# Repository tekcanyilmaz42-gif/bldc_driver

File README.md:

# BLDC / PMSM Motor Driver AI (KiCad 10 Project)

Bu depo, modüler BLDC / PMSM ve EESM motor sürücüsü donanım tasarımını (KiCad 10) içermektedir.

## 📁 Proje Yapısı

- `bldc_driver_ai.kicad_pro` / `.kicad_sch` / `.kicad_pcb`: Ana sistem projesi ve üst seviye bağlantılar
- `kontrol_karti.kicad_sch`: dsPIC tabanlı kontrol kartı şematiği
- `guc_karti.kicad_sch`: TO-220 MOSFET tabanlı yüksek akım güç katı ve 24× KOSHIN KLH (24 mF, 60 A rms) DC-link bara kondansatör grubu
- `gate_driver_u.kicad_sch`, `gate_driver_v.kicad_sch`, `gate_driver_w.kicad_sch`: Faz sürücü modülleri
- `eesm_modulu.kicad_sch`: EESM uyarma kontrol modülü
- `bldc_proje.pretty/` & `fp-lib-table`: Projeye özel footprint kütüphanesi (KOSHIN KLH radial elektrolitik, özel land pattern'ler)
- `montaj/`: 3D montaj modelleri (`.step`), mekanik yerleşim ve render görselleri
- `uretim/`: Modüllere ait üretim Gerber arşivleri (`.zip`), klasörleri ve SMD dizgi koordinat listeleri (`.csv`)
- `yardımcı_dokuman/`: Revizyon raporları, teknik analizler ve destekleyici dokümanlar
- `bldc_driver_ai_BOM.xlsx`: Güncel malzeme listesi (BOM)
- `SISTEM_REVIZYON_PLANI.md`: Kapsamlı sistem revizyon ve doğrulama planı

## 🛠️ Gereksinimler

- [KiCad 10.0+](https://www.kicad.org/) veya uyumlu sürüm

## 🔍 Tasarım İncelemesi 3: Bulgular ve Yapılan Değişiklikler

Bu bölüm, 3. tasarım incelemesinde açık kalan maddeleri ve her biri için verilen kararı özetler. Ayrıntılar `SISTEM_REVIZYON_PLANI.md` §2.21'dedir. Değişiklik öncesi yedek `yedek_faz7/pre_inceleme3/` klasöründedir.

**Doğrulama:** DRC 0 hata, kart içi bağlanmamış nokta 0, şematik–PCB eşleşmesi tam; ERC'de yalnızca bilinen 4 TJA1051 uyarısı var.

### 1. Harici 12 V girişi

**Bulgu:** Önceki incelemede söylenen üç madde şematikte düzeltilmemişti:
- D43 (TVS) F1'in önündeydi.
- U21 (5 V LDO) aşırı gerilime karşı korumasızdı.
- F1 (PTC) sıcakta kendiliğinden atabilir.

**Yapılan:**
- **D43 F1'in arkasına alındı.** D43'ün katodu artık 12V_EXT hattında. Uzun süren aşırı gerilimde TVS iletime geçiyor ve F1 atıyor; TVS yanmıyor.
- Kartta D43, D42'nin yanına (322.6, 17.6) taşındı ve 12V_EXT'e alt katmandan kısa bir köprüyle bağlandı. Eski izler silindi.

**Bilerek değiştirilmeyenler (açık madde):**
- **U21:** hâlâ 12 V hattından besleniyor. Önerilen çözüm, U21'i kaldırıp CAN alıcısını mevcut 5V_SYS hattından beslemek.
- **F1 (PTC):** sıcakta değer kaybettiği için kutu içi sıcaklıkta erken atabilir. Prototipte kontrol edilmeli; gerekirse daha yüksek akımlı bir PTC veya cam sigorta kullanılabilir.

### 2. VBAT ve GND pabuçları arası 15 mm

**Bulgu:** 100 A için kullanılan 25–35 mm² pabuçlar 12–15 mm genişliğinde. Pabuçlar dönerse birbirine değebilir ve bataryayı kısa devre eder.

**Yapılan:** Mesafe korundu, izolasyon zorunlu hale getirildi:
- BOM'un mekanik sayfasına zorunlu bir satır eklendi: J1 (VBAT) ve J2 (GND) pabuçlarının ikisine de kalın makaron (ısıyla daralan) veya izolasyon başlığı geçirilecek.
- Güç kartında J1'in altına ipek baskı uyarısı eklendi: `J1/J2 PABUC: MAKARON VEYA BASLIK ZORUNLU`.

### 3. Kondansatörlerin MOSFET'lerin üstünde olması

**Bulgu:**
- Kondansatör bacak ucu ile MOSFET gövdesi arasında yalnızca yaklaşık 0.7 mm boşluk vardı (2.2 mm aralık, eksi 1.5 mm kesilmiş bacak).
- MOSFET ısısı kondansatörleri ısıtır ve ömürlerini kısaltır.
- Arızalı bir MOSFET'i değiştirmek için 24 kondansatörlü kartın tamamı sökülmeli.

**Yapılan:**
- **Kart, soğutucunun 8.5 mm üstüne çıkarıldı** (önceden 7 mm). Plastik gövde ile kart arası artık 3.7 mm. Bacaklar 1.5 mm kesildiğinde yaklaşık 2.2 mm pay kalıyor. MOSFET bacak boyu bu yüksekliğe yetiyor.
- Montaj modeli (`montaj/`) ve BOM'daki ara parçalar (M3 vida + 8.5 mm ara parça) güncellendi.

**Açık kalanlar:**
- **Sıcaklık:** 5 kW'ta kondansatör gövde sıcaklığı prototipte ölçülmeli.
- **Servis:** MOSFET değişimi için kartın sökülmesi gerekiyor. Bu bir tasarım hatası değil, yerleşimin kabul edilmiş bir sonucu.

### 4. Motor tarafı

**Bulgu:** Hall sensörü için 5 V besleme ve motor sıcaklık sensörü için giriş yoktu.

**Karar:** Hall sensörü yerine enkoder kullanılacak.

**Enkoder:**
- Besleme 3.3 V olarak kaldı.
- Seri dirençler R71, R73 ve R75 100 Ω'dan 1 kΩ'a çıkarıldı. 5 V çıkışlı bir enkoder takılsa bile MCU pinine giren akım yaklaşık 1.4 mA'de kalır; sınır 5 mA.

**Motor sıcaklık girişi (yeni):**
- **Konnektör:** J52 "Motor_Sicaklik" (1×02 pin header). Pin 1 NTC_MOT, pin 2 GND. Kontrol kartının üst kenarında, enkoder soketinin sağında.
- **Devre:**
  - R145: 2.2 kΩ %0.1 pull-up (3V3_ANA hattına). Hem 10k NTC hem de KTY84-130 sensörüyle çalışır.
  - R146: 22 kΩ seri koruma direnci. Sargı yalıtımı bozulup hatta 60 V gelse bile pine giren akımı yaklaşık 2.6 mA'de tutar.
  - C224: 100 nF filtre.
- **MCU bağlantısı:** U6 pin 40 (**AN16**/RC7). Firmware'de ADC kanalı AN16 olarak tanımlanmalı.
  - Önce pin 19 (AN23) planlandı, ancak dar pin aralığı yüzünden iz çıkarılamadı.
  - Yeni iz U6'nın altındaki GND adasını ana GND'den ayırdığı için üst katmana bir GND köprüsü eklendi.

### Teyit bekleyen maddeler

Motor datasheet'i (`QS 48V 5000W 690RPM V3.pdf`) okunamadı. Aşağıdakiler motor kablosuna ve datasheet'e göre doğrulanmalı:
- Motor sıcaklık sensörünün tipi (NTC veya KTY84) ve J52 pin dizilimi.
- Enkoderin 3.3 V beslemeyle çalışıp çalışmadığı.

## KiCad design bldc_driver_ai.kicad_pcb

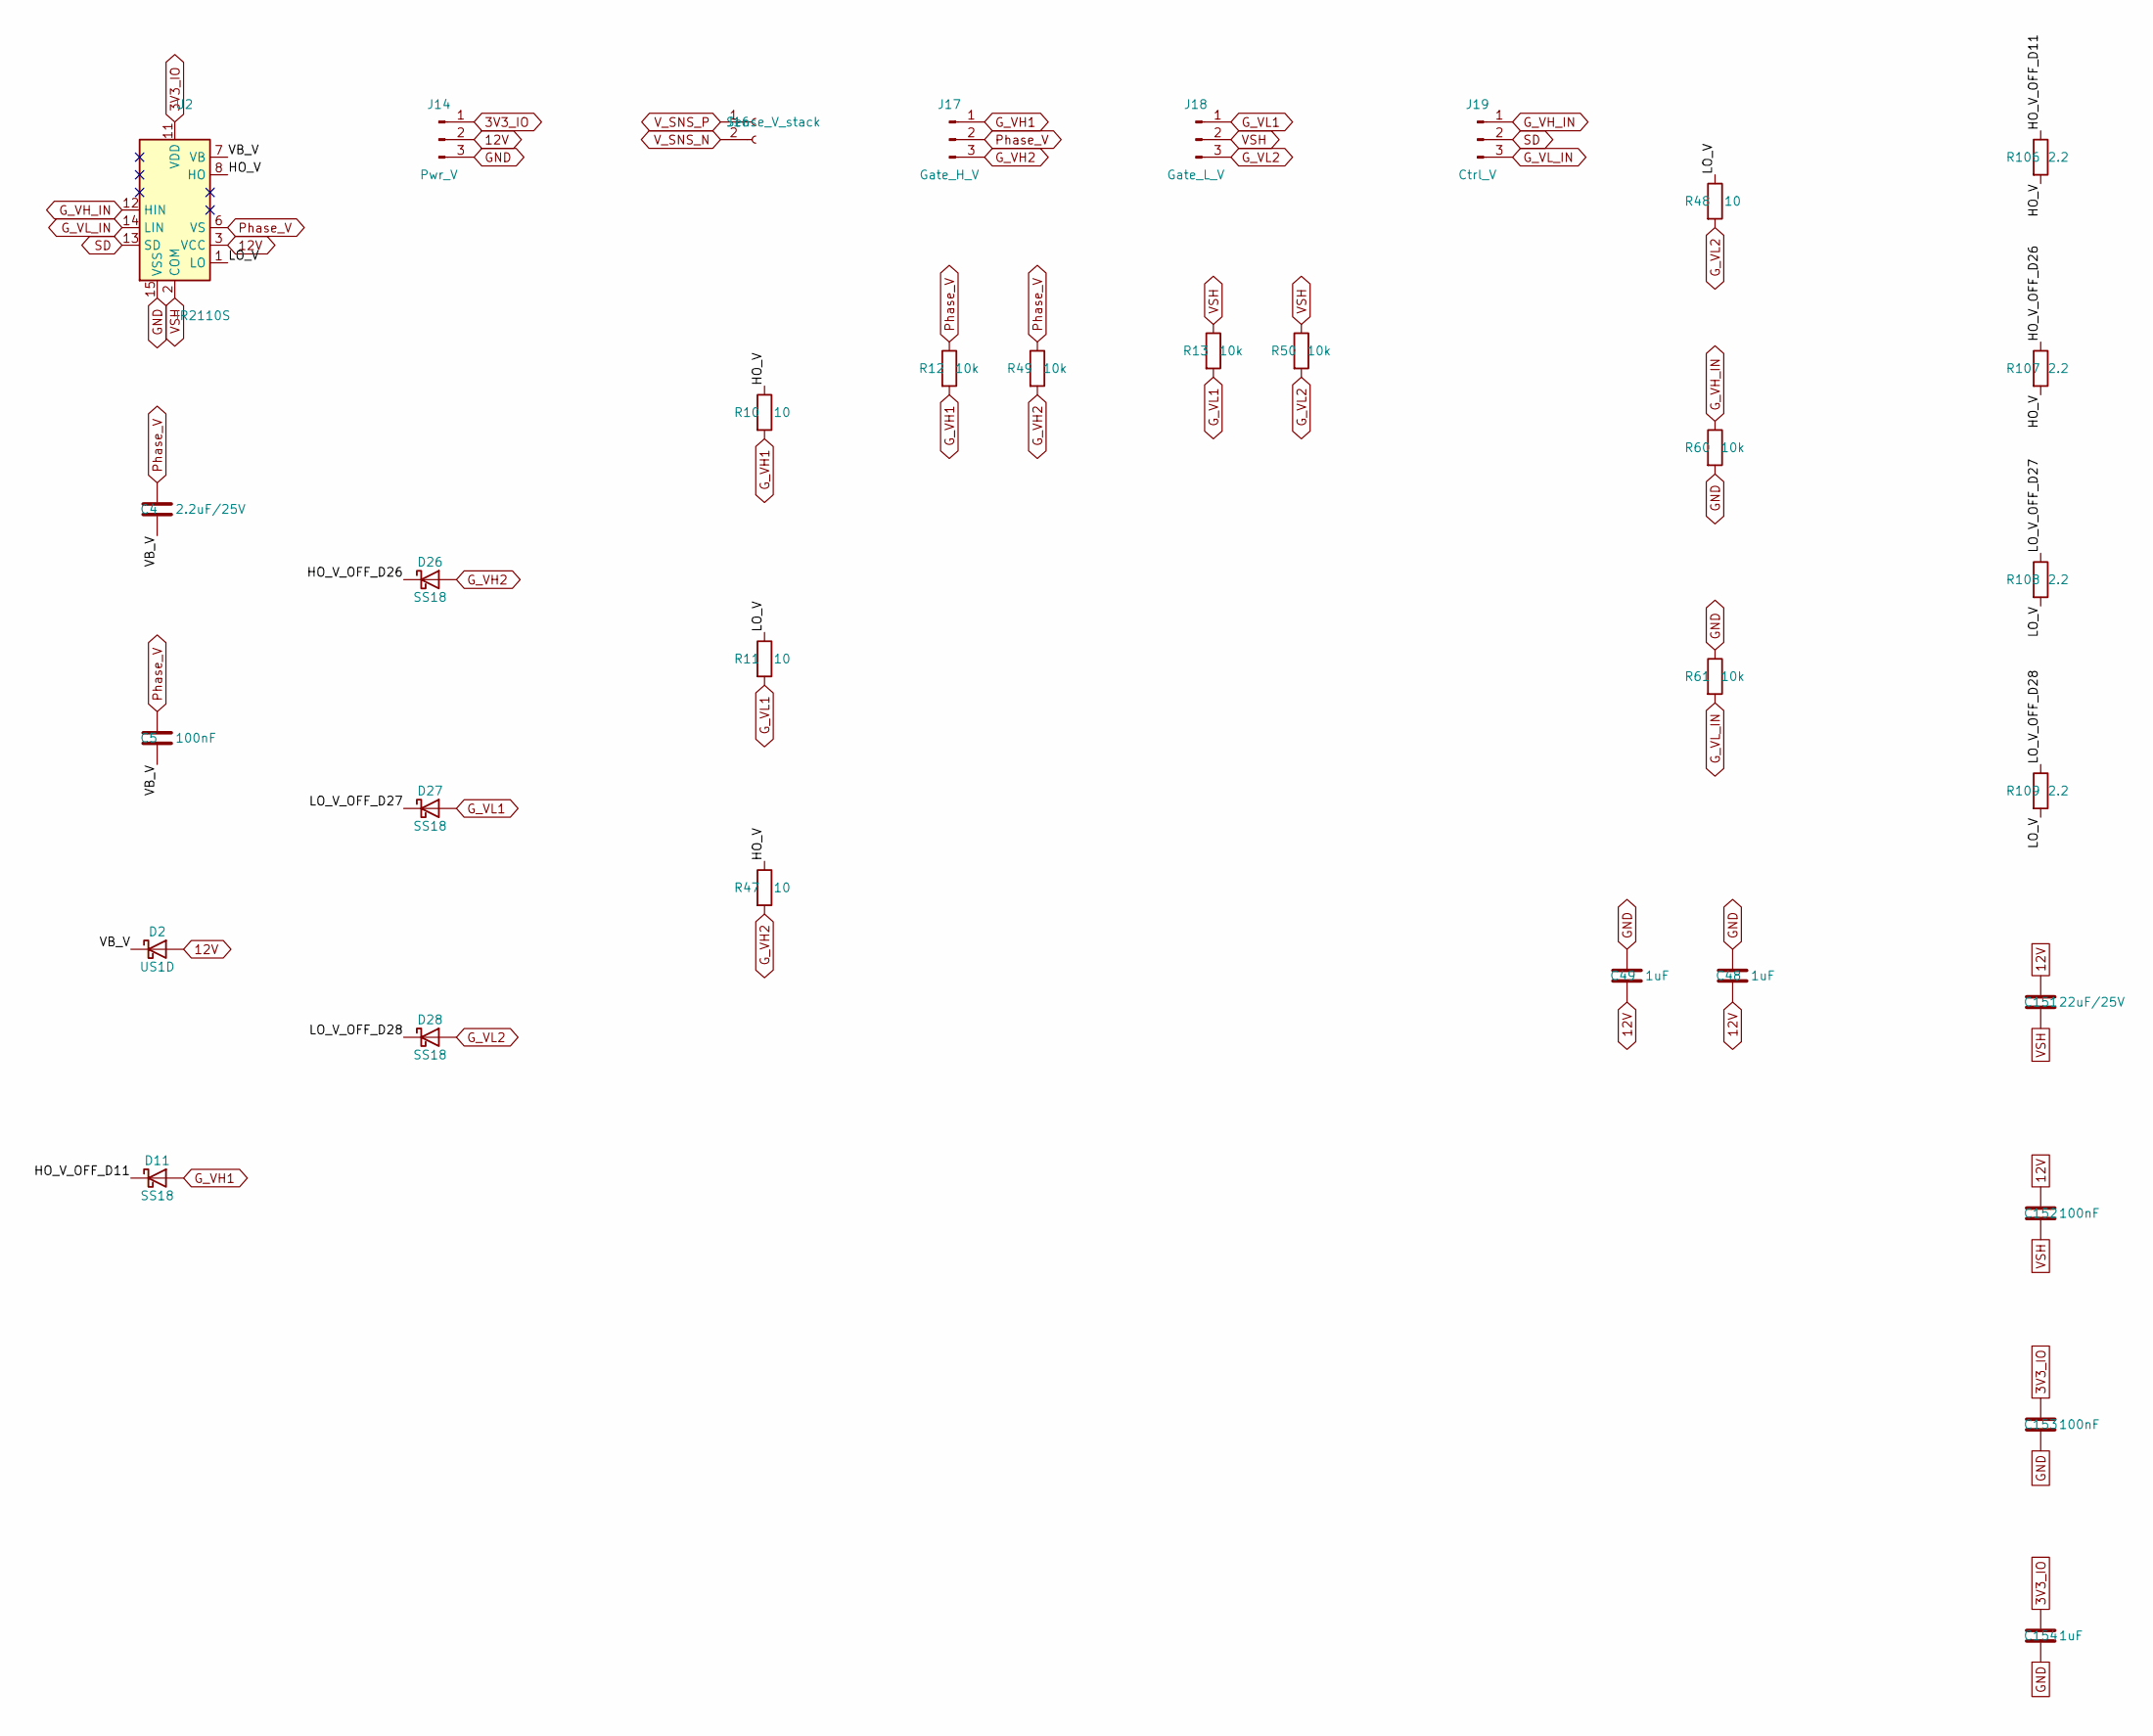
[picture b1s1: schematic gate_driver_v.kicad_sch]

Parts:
C4: 2.2uF/25V; C_1206_3216Metric; MPN CL31B225KAHNNNE
C5, C152, C153: 100nF; C_0603_1608Metric
C48, C49, C154: 1uF; C_0603_1608Metric
C151: 22uF/25V; C_1206_3216Metric; MPN CL31A226KAHNNNE
D2: US1D; D_SMA; MPN US1D-13-F
D11, D26, D27, D28: SS18; D_SMA
J14: Pwr_V; PinHeader_1x03_P2.54mm_Vertical
J16: Sense_V_stack; PinSocket_1x02_P2.54mm_Vertical
J17: Gate_H_V; PinHeader_1x03_P2.54mm_Vertical
J18: Gate_L_V; PinHeader_1x03_P2.54mm_Vertical
J19: Ctrl_V; PinHeader_1x03_P2.54mm_Vertical
R10, R11, R47, R48: 10; R_0805_2012Metric
R12, R13, R49, R50, R60, R61: 10k; R_0603_1608Metric
R106, R107, R108, R109: 2.2; R_0603_1608Metric
U2: IR2110S; SOIC-16W_7.5x10.3mm_P1.27mm

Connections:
3V3_IO: C153.1, C154.1, J14.1, U2.11 (VDD); also elsewhere on the board
12V: C48.2, C49.2, C151.1, C152.1, D2.2 (A), J14.2, U2.3 (VCC); also elsewhere on the board
/Katman2_GateDriver_V/HO_V: R10.1, R47.1, R106.2, R107.2, U2.8 (HO)
/Katman2_GateDriver_V/HO_V_OFF_D11: D11.1 (K), R106.1
/Katman2_GateDriver_V/HO_V_OFF_D26: D26.1 (K), R107.1
/Katman2_GateDriver_V/LO_V: R11.1, R48.1, R108.2, R109.2, U2.1 (LO)
/Katman2_GateDriver_V/LO_V_OFF_D27: D27.1 (K), R108.1
/Katman2_GateDriver_V/LO_V_OFF_D28: D28.1 (K), R109.1
/Katman2_GateDriver_V/VB_V: C4.2, C5.2, D2.1 (K), U2.7 (VB)
GND: C48.1, C49.1, C153.2, C154.2, J14.3, R60.2, R61.1, U2.15 (VSS); also elsewhere on the board
G_VH1: D11.2 (A), J17.1, R10.2, R12.2; also elsewhere on the board
G_VH2: D26.2 (A), J17.3, R47.2, R49.2; also elsewhere on the board
G_VH_IN: J19.1, R60.1, U2.12 (HIN); also elsewhere on the board
G_VL1: D27.2 (A), J18.1, R11.2, R13.2; also elsewhere on the board
G_VL2: D28.2 (A), J18.3, R48.2, R50.2; also elsewhere on the board
G_VL_IN: J19.3, R61.2, U2.14 (LIN); also elsewhere on the board
Phase_V: C4.1, C5.1, J17.2, R12.1, R49.1, U2.6 (VS); also elsewhere on the board
SD: J19.2, U2.13 (SD); also elsewhere on the board
VSH: C151.2, C152.2, J18.2, R13.1, R50.1, U2.2 (COM); also elsewhere on the board
V_SNS_N: J16.2; also elsewhere on the board
V_SNS_P: J16.1; also elsewhere on the board
